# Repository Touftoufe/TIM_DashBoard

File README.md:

# TIM_DashBoard
TIM's new cars' dashboards

## Project Information

## Organization tree
 
 - hardware 
    - doc
        - BOM
        - appnotes
        - datasheets
        - errata
    - kicad
        - [inventhub git](https://inventhub.io/c/elprincipito/TIM_DashBoard/tree/default) (hardware versions management) 
        - project library
        - schematic
        - layout
    - meca
        - 3d models
        - gerber
- software
    - STM32CubeIDE project*  
- documentation
    - Block diagram
    - ICD (Interface control document)
    - User manual
    - Pinion diagram

## 'Requirements' specification

### Indispensable requirements
- See `actual` speed on screen
- Switch headlight on or off
- Signal turn (left, right, switch off)
- Wipe the windshield
- See break light status on screen
- Select wiper speed
- Select power level

### Optional requirements
- Select speed limit
- See set speed limit on screen
- Choose to drive forward or in reverse
- Turn car on/Off
- Configuration interface to choose between different modes

### Out of scope
- Klaxon

##  Progress status 
- [x] Organize the project
- [x] Have a clear idea of what to make
- [x] Test all hardware functions on prototype board
- [x] Correct the mistakes on prototype board 
- [x] Write and update Errata (/hardware/doc/errata.md)
- [x] Complete the specifications
- [ ] Translate the specifications into sequence diagram
- [ ] Start software for different functions
    - [ ] epaper screen control
    - [ ] servo motor control
    - [ ] speed limit input
    - [ ] menu navigation
    - [ ] *gpio* Lights control
    - [ ] *gpio* ...
- [ ] Document the [source code](/software) 
- [ ] Pass the tests
- [ ] write a User manual 
- [ ] Insatll new dashboard in the car 

## Contributors 
[Aouci Sofiane](https://www.linkedin.com/in/sofiane-aouci/) 

[Jacquet Prince](http://www.jacquet.live)

For Team : [TIM UPS INSA](http://www.timupsinsa.com)

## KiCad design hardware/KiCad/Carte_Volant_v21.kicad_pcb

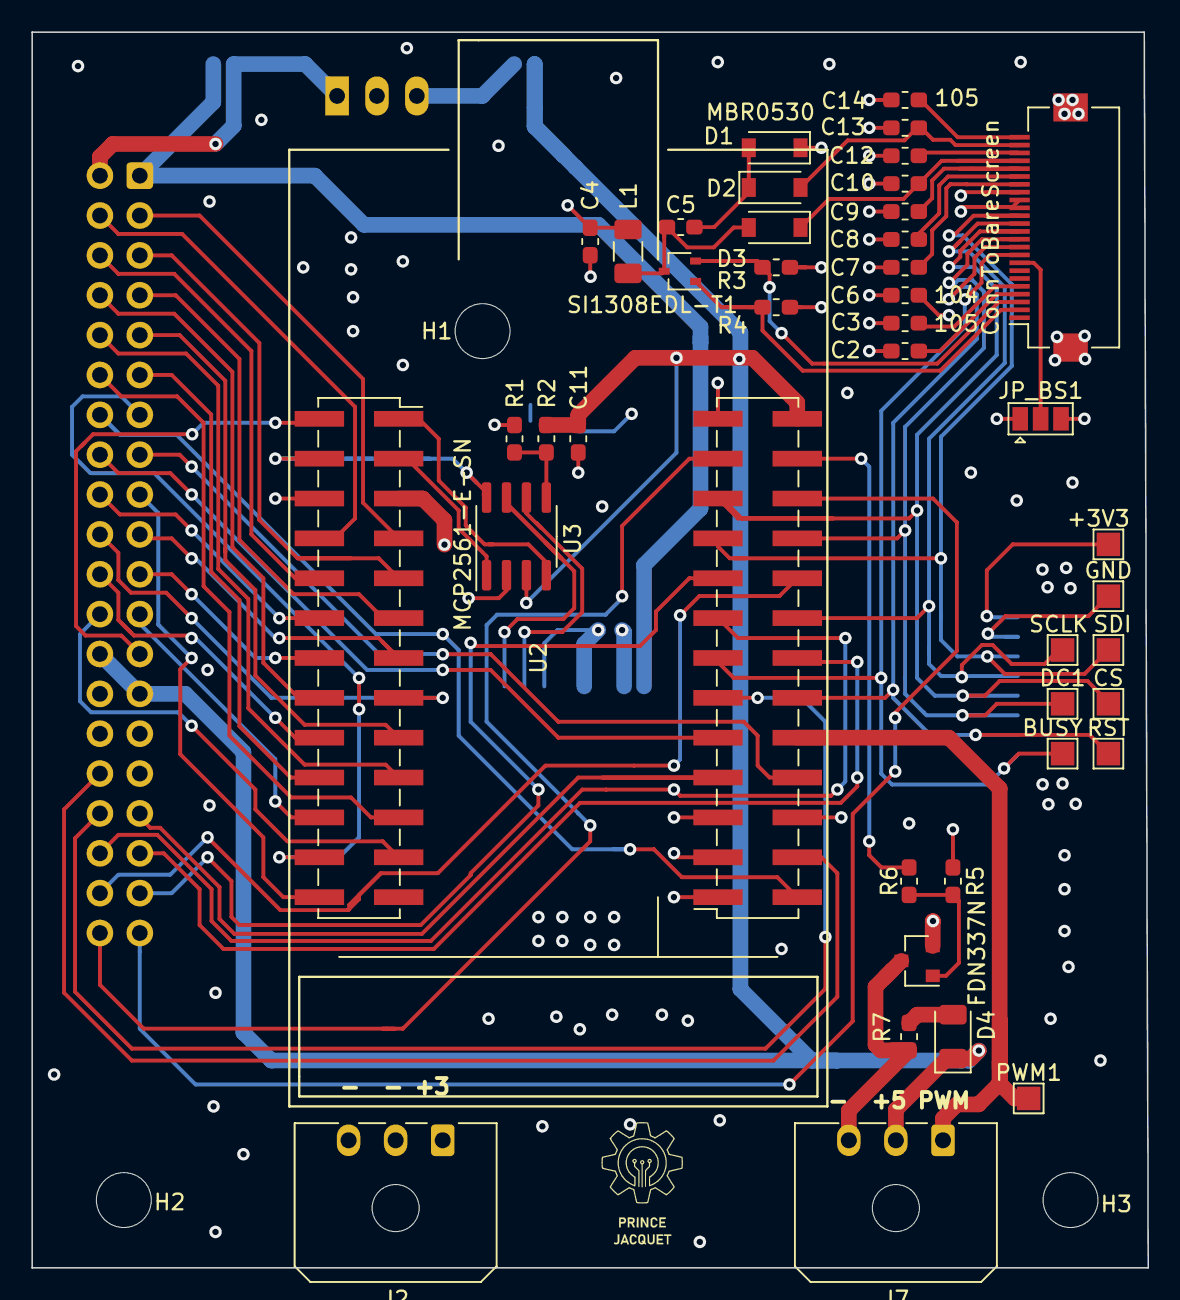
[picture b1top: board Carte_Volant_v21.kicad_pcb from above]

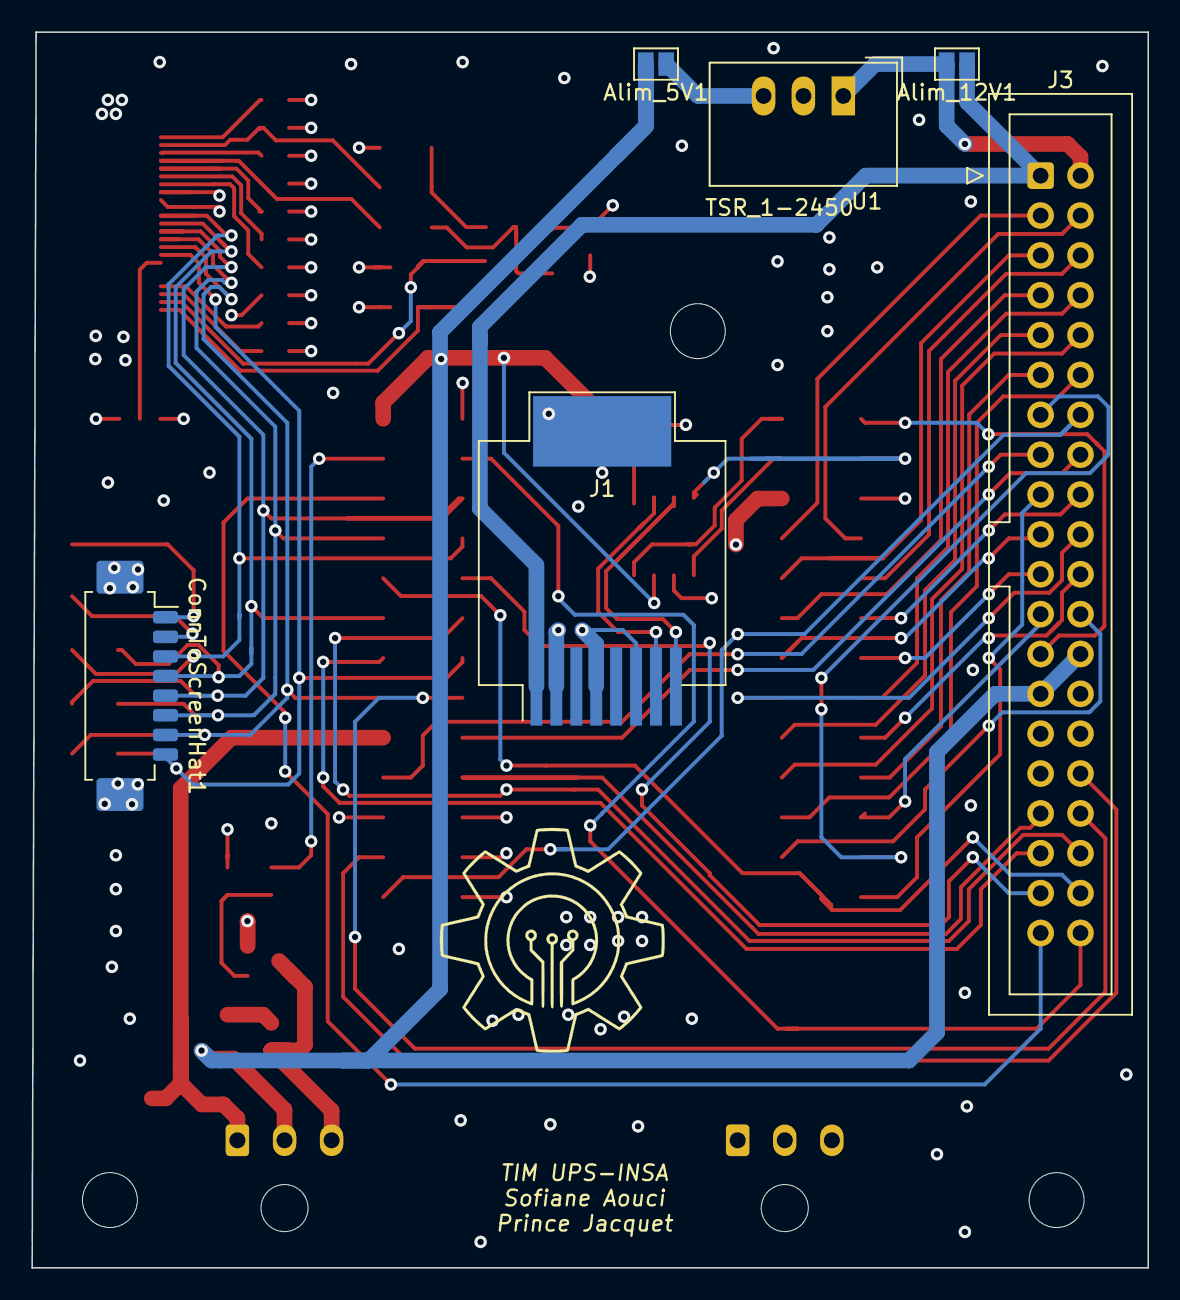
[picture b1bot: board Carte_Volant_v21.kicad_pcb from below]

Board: 4 copper layers, 71.1 x 78.7 mm, 51 parts (6 on the bottom side), 69 nets.

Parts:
+3V3: TestPoint; TestPoint_Pad_1.5x1.5mm
Alim_5V1, Alim_12V1: Jumper_NO_Small; SolderJumper-2_P1.3mm_Open_Pad1.0x1.5mm
BUSY: TestPoint; TestPoint_Pad_1.5x1.5mm
C2, C3, C7, C8, C9, C10, C12, C13, C14: 105; C_0603_1608Metric_Pad1.05x0.95mm_HandSolder
C4, C5: 4.7u; C_0603_1608Metric_Pad1.05x0.95mm_HandSolder
C6: 104; C_0603_1608Metric_Pad1.05x0.95mm_HandSolder
C11: 100n; C_0603_1608Metric_Pad1.05x0.95mm_HandSolder
CS: TestPoint; TestPoint_Pad_1.5x1.5mm
ConnToBareScreen: FFC_PFC_Conn_01x24_0.5MM; Hirose_FH12-24S-0.5SH_1x24-1MP_P0.50mm_Horizontal
ConnToScreenHat1: Conn_01x08; Molex_PicoBlade_53261-0871_1x08-1MP_P1.25mm_Horizontal
D1, D2, D3: MBR0530; D_SOD-123
D4: D; D_1206_3216Metric
DC1: TestPoint; TestPoint_Pad_1.5x1.5mm
GND: TestPoint; TestPoint_Pad_1.5x1.5mm
H1, H2, H3: MountingHole; MountingHole_3.5mm
J1: RJ45_CANBUS; RJ45_Molex_0855135013_Vertical
J2, J7: Conn_01x03; Molex_Micro-Fit_3.0_43650-0300_1x03_P3.00mm_Horizontal
J3: Conn_01x40; IDC-Header_2x20_P2.54mm_Vertical
JP_BS1: SolderJumper_3_Open; SolderJumper-3_P1.3mm_Open_Pad1.0x1.5mm
L1: L_Core_Ferrite; L_1206_3216Metric
PWM1: TestPoint; TestPoint_Pad_1.5x1.5mm
Q2: FDN337N; SOT-23
R1, R2, R4, R5, R7: 10k; R_0603_1608Metric_Pad1.05x0.95mm_HandSolder
R3: 47r; R_0603_1608Metric_Pad1.05x0.95mm_HandSolder
R6: 10; R_0603_1608Metric_Pad1.05x0.95mm_HandSolder
RST: TestPoint; TestPoint_Pad_1.5x1.5mm
SCLK: TestPoint; TestPoint_Pad_1.5x1.5mm
SDI: TestPoint; TestPoint_Pad_1.5x1.5mm
SI1308EDL-T1: Si1304BDL; SOT-323_SC-70
U1: TSR_1-2450; Converter_DCDC_TRACO_TSR-1_THT
U2: STM32H103-OlimexBoard; STM32H103-Olimex_SMD
U3: MCP2561-E-SN; SOIC-8_3.9x4.9mm_P1.27mm

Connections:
5VUSB: J3.40, U2.49
+3V3: +3V3.1, C4.2, C6.2, ConnToBareScreen.15, ConnToBareScreen.16, ConnToScreenHat1.1, J2.1, J3.30, J3.31, JP_BS1.1, L1.1, U2.5, U2.27, U2.31
+5V: Alim_5V1.2, C11.2, D4.1, J3.26, J3.27, J7.2, R2.1, U2.52, U3.3
+12V: Alim_12V1.1, J1.8, J3.1
ADC_current_Selector: J3.4, U2.8
BRAKE: J3.6, U2.10
BS: ConnToBareScreen.8, JP_BS1.2
BUSY: BUSY.1, ConnToBareScreen.9, ConnToScreenHat1.8, U2.39
CANH: J1.1, U3.7
CANL: J1.2, U3.6
CAN_Rx: U2.1, U3.4
CAN_STBY: U2.4, U3.8
CAN_Tx: U2.3, U3.1
CS: CS.1, ConnToBareScreen.12, ConnToScreenHat1.5, U2.47
D_C: ConnToBareScreen.11, ConnToScreenHat1.6, DC1.1, U2.46
ENC_SpeedSelector_CCW: J3.9, U2.17
ENC_SpeedSelector_CW: J3.8, U2.16
ENC_SpeedSelector_ok: J3.7, U2.11
GDR: ConnToBareScreen.2, R4.1, SI1308EDL-T1.1
GND: C2.1, C3.1, C4.1, C6.1, C7.1, C8.1, C9.1, C10.1, C11.1, C12.1, C13.1, C14.1, ConnToBareScreen.17, ConnToScreenHat1.2, D1.1, GND.1, J1.3, J1.5, J1.7, J1.L, J2.2, J2.3, J3.28, J3.29, JP_BS1.3, Q2.2, R1.2, R3.2, R4.2, R5.1, U1.2, U2.6, U2.29, U2.32, U2.51, U3.2
LIGHTS_Back: J3.11, U2.20
LIGHTS_Front: J3.10, U2.19
Marche_AVNT-ARRIER: J3.3, U2.7
unnamed: Alim_5V1.1, U1.3
unnamed: C5.1, D3.2, L1.2, SI1308EDL-T1.3
unnamed: C5.2, D1.2, D2.1
unnamed: D4.2, R7.1
unnamed: J7.3, Q2.3, R7.2
unnamed: Q2.1, R5.2, R6.1
unnamed: R1.1, R2.2, U3.5
PA0: J3.32, U2.30
PA2: J3.33, U2.33
PA4: J3.34, U2.37
PA5: J3.22, U2.18
PA6: J3.21, U2.14
PA7: J3.23, U2.22
PA8: J3.25, U2.2
PB5: J3.18, U2.12
PB6: J3.19, U2.13
PB7: J3.20, U2.15
PB10: J3.35, U2.40
PB11: J3.36, U2.41
PB12: J3.37, U2.43
PB14: J3.38, U2.44
PC8: J3.39, U2.48
POWER_SWITCH: Alim_12V1.2, J3.2, U1.1
PREVGH: C10.2, ConnToBareScreen.21, D3.1
PREVGL: C13.2, ConnToBareScreen.23, D2.2
PWM_wiper: J7.1, PWM1.1, U2.36
RESE: ConnToBareScreen.3, R3.1, SI1308EDL-T1.2
RST: ConnToBareScreen.10, ConnToScreenHat1.7, RST.1, U2.38
SCLK: ConnToBareScreen.13, ConnToScreenHat1.4, SCLK.1, U2.42
SDI: ConnToBareScreen.14, ConnToScreenHat1.3, SDI.1, U2.45
TURN_Sgnl_LEFT: J3.13, U2.24
TURN_Sgnl_RIGHT: J3.12, U2.21
VBAT: J3.24, U2.23
VCOM: C14.2, ConnToBareScreen.24
VDD: C7.2, ConnToBareScreen.18
VGH: C3.2, ConnToBareScreen.5
VGL: C2.2, ConnToBareScreen.4
VPP: C8.2, ConnToBareScreen.19
VSH: C9.2, ConnToBareScreen.20
VSL: C12.2, ConnToBareScreen.22
accelerateur: J3.5, U2.9
menu_down: J3.16, U2.35
menu_ok: J3.14, U2.28
menu_up: J3.15, U2.34
power_wiper: R6.2, U2.50
wiper_speed: J3.17, U2.26

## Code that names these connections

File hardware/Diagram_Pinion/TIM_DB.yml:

name: Carte_Volant_v21  # Put the name of diagram here
description: Example diagram # Put a short description of the diagram here
components:
    J1:
        description: RJ45_CANBUS_copy  # Arbitrary comment
        groups: [] # Specify component groups
        pins:
            L:  # Connected to GND
                name: J1.L
                description: ''
                groups: []
            '8': # Connected to -POWER_ON-OFF
                name: J1.8
                description: ''
                groups: []
            '7': # Connected to GND
                name: J1.7
                description: ''
                groups: []
            '6': # Connected to Net-(J1-Pad6)
                name: J1.6
                description: ''
                groups: []
            '5': # Connected to GND
                name: J1.5
                description: ''
                groups: []
            '4': # Connected to Net-(J1-Pad4)
                name: J1.4
                description: ''
                groups: []
            '3': # Connected to GND
                name: J1.3
                description: ''
                groups: []
            '2': # Connected to CANL
                name: J1.2
                description: ''
                groups: []
            '1': # Connected to CANH
                name: J1.1
                description: ''
                groups: []
        highlight: false # Make the component active
    U2:
        description: STM32H103-OlimexBoard  # Arbitrary comment
        groups: [] # Specify component groups
        pins:
            '27':  # Connected to +3V3
                name: U2.27
                description: ''
                groups: []
            '50': # Connected to power_wiper
                name: U2.50
                description: ''
                groups: []
            '48': # Connected to PC8
                name: U2.48
                description: ''
                groups: []
            '37': # Connected to PA4
                name: U2.37
                description: ''
                groups: []
            '34': # Connected to menu_up
                name: U2.34
                description: ''
                groups: []
            '47': # Connected to CS
                name: U2.47
                description: ''
                groups: []
            '45': # Connected to SDI
                name: U2.45
                description: ''
                groups: []
            '40': # Connected to PB10
                name: U2.40
                description: ''
                groups: []
            '36': # Connected to PWM_wiper
                name: U2.36
                description: ''
                groups: []
            '28': # Connected to menu_ok
                name: U2.28
                description: ''
                groups: []
            '29': # Connected to GND
                name: U2.29
                description: ''
                groups: []
            '49': # Connected to 5VUSB
                name: U2.49
                description: ''
                groups: []
            '33': # Connected to PA2
                name: U2.33
                description: ''
                groups: []
            '42': # Connected to SCLK
                name: U2.42
                description: ''
                groups: []
            '31': # Connected to +3V3
                name: U2.31
                description: ''
                groups: []
            '39': # Connected to BUSY
                name: U2.39
                description: ''
                groups: []
            '38': # Connected to RST
                name: U2.38
                description: ''
                groups: []
            '46': # Connected to D_C
                name: U2.46
                description: ''
                groups: []
            '41': # Connected to PB11
                name: U2.41
                description: ''
                groups: []
            '32': # Connected to GND
                name: U2.32
                description: ''
                groups: []
            '30': # Connected to PA0
                name: U2.30
                description: ''
                groups: []
            '44': # Connected to PB14
                name: U2.44
                description: ''
                groups: []
            '43': # Connected to PB12
                name: U2.43
                description: ''
                groups: []
            '35': # Connected to menu_down
                name: U2.35
                description: ''
                groups: []
            '52': # Connected to +5V
                name: U2.52
                description: ''
                groups: []
            '51': # Connected to GND
                name: U2.51
                description: ''
                groups: []
            '1': # Connected to CAN_Rx
                name: U2.1
                description: ''
                groups: []
            '24': # Connected to TURN_Sgnl_LEFT
                name: U2.24
                description: ''
                groups: []
            '22': # Connected to PA7
                name: U2.22
                description: ''
                groups: []
            '11': # Connected to ENC_SpeedSelector_ok
                name: U2.11
                description: ''
                groups: []
            '8': # Connected to ADC_current_Selector
                name: U2.8
                description: ''
                groups: []
            '21': # Connected to TURN_Sgnl_RIGHT
                name: U2.21
                description: ''
                groups: []
            '19': # Connected to LIGHTS_Front
                name: U2.19
                description: ''
                groups: []
            '14': # Connected to PA6
                name: U2.14
                description: ''
                groups: []
            '10': # Connected to BRAKE
                name: U2.10
                description: ''
                groups: []
            '2': # Connected to PA8
                name: U2.2
                description: ''
                groups: []
            '3': # Connected to CAN_Tx
                name: U2.3
                description: ''
                groups: []
            '23': # Connected to VBAT
                name: U2.23
                description: ''
                groups: []
            '7': # Connected to Marche_AVNT-ARRIER
                name: U2.7
                description: ''
                groups: []
            '16': # Connected to ENC_SpeedSelector_CW
                name: U2.16
                description: ''
                groups: []
            '5': # Connected to +3V3
                name: U2.5
                description: ''
                groups: []
            '13': # Connected to PB6
                name: U2.13
                description: ''
                groups: []
            '12': # Connected to PB5
                name: U2.12
                description: ''
                groups: []
            '20': # Connected to LIGHTS_Back
                name: U2.20
                description: ''
                groups: []
            '15': # Connected to PB7
                name: U2.15
                description: ''
                groups: []
            '6': # Connected to GND
                name: U2.6
                description: ''
                groups: []
            '4': # Connected to CAN_STBY
                name: U2.4
                description: ''
                groups: []
            '18': # Connected to PA5
                name: U2.18
                description: ''
                groups: []
            '17': # Connected to ENC_SpeedSelector_CCW
                name: U2.17
                description: ''
                groups: []
            '9': # Connected to accelerateur
                name: U2.9
                description: ''
                groups: []
            '26': # Connected to wiper_speed
                name: U2.26
                description: ''
                groups: []
            '25': # Connected to ST_RST
                name: U2.25
                description: ''
                groups: []
        highlight: false # Make the component active

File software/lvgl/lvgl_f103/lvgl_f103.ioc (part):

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Mcu.Name=STM32F103R(8-B)Tx
Mcu.Package=LQFP64
Mcu.UserName=STM32F103RBTx
PA11.Mode=CAN_Activate
PA11.Signal=CAN_RX
PA12.Mode=CAN_Activate
PA12.Signal=CAN_TX
PA13.Mode=Serial_Wire
PA13.Signal=SYS_JTMS-SWDIO
PA14.Mode=Serial_Wire
PA14.Signal=SYS_JTCK-SWCLK
PA3.GPIOParameters=GPIO_Label
PA3.GPIO_Label=timer_pwm
PA3.Signal=S_TIM2_CH4
PA4.GPIOParameters=GPIO_Label
PA4.GPIO_Label=CurrentSelector
PA4.Signal=SharedAnalog_PA4
PA5.Mode=Full_Duplex_Master
PA5.Signal=SPI1_SCK
PA6.Mode=Full_Duplex_Master
PA6.Signal=SPI1_MISO
PA7.Mode=Full_Duplex_Master
PA7.Signal=SPI1_MOSI
PA9.GPIOParameters=GPIO_Label
PA9.GPIO_Label=CAN_STBY
PA9.Signal=GPIO_Output
PB0.GPIOParameters=GPIO_Label
PB0.GPIO_Label=LCD_RST
PB0.Signal=GPIO_Output
PB10.GPIOParameters=GPIO_Label
PB10.GPIO_Label=LCD_DC
PB10.Signal=GPIO_Output
PB12.GPIOParameters=GPIO_PuPd,GPIO_Label,GPIO_ModeDefaultEXTI
PB12.GPIO_Label=WiperStateB
PB12.GPIO_ModeDefaultEXTI=GPIO_MODE_IT_RISING_FALLING
PB12.GPIO_PuPd=GPIO_PULLUP
PB12.Signal=GPXTI12
PB14.GPIOParameters=GPIO_PuPd,GPIO_Label,GPIO_ModeDefaultEXTI
PB14.GPIO_Label=WiperStateA
PB14.GPIO_ModeDefaultEXTI=GPIO_MODE_IT_RISING_FALLING
PB14.GPIO_PuPd=GPIO_PULLUP
PB14.Signal=GPXTI14
PB5.GPIOParameters=GPIO_PuPd,GPIO_Label,GPIO_ModeDefaultEXTI
PB5.GPIO_Label=Left_TurnSignal
PB5.GPIO_ModeDefaultEXTI=GPIO_MODE_IT_RISING_FALLING
PB5.GPIO_PuPd=GPIO_PULLUP
PB5.Signal=GPXTI5
PB6.GPIOParameters=GPIO_PuPd,GPIO_Label,GPIO_ModeDefaultEXTI
PB6.GPIO_Label=Right_TurnSignal
PB6.GPIO_ModeDefaultEXTI=GPIO_MODE_IT_RISING_FALLING
PB6.GPIO_PuPd=GPIO_PULLUP
PB6.Signal=GPXTI6
PC1.GPIOParameters=GPIO_PuPd,GPIO_Label,GPIO_ModeDefaultEXTI
PC1.GPIO_Label=HeadLight
PC1.GPIO_ModeDefaultEXTI=GPIO_MODE_IT_RISING_FALLING
PC1.GPIO_PuPd=GPIO_PULLUP
PC1.Signal=GPXTI1
PC12.GPIOParameters=GPIO_Label
PC12.GPIO_Label=LED
PC12.Signal=GPIO_Output
PC5.GPIOParameters=GPIO_Label
PC5.GPIO_Label=SPI_CS
PC5.Signal=GPIO_Output
PC8.GPIOParameters=GPIO_PuPd,GPIO_Label,GPIO_ModeDefaultEXTI
PC8.GPIO_Label=BreakPedal
PC8.GPIO_ModeDefaultEXTI=GPIO_MODE_IT_RISING_FALLING
PC8.GPIO_PuPd=GPIO_PULLUP
PC8.Signal=GPXTI8
PD0-OSC_IN.Mode=HSE-External-Oscillator
PD0-OSC_IN.Signal=RCC_OSC_IN
PD1-OSC_OUT.Mode=HSE-External-Oscillator
PD1-OSC_OUT.Signal=RCC_OSC_OUT
PD2.GPIOParameters=GPIO_PuPd,GPIO_Label,GPIO_ModeDefaultEXTI
PD2.GPIO_Label=Accelerator
PD2.GPIO_ModeDefaultEXTI=GPIO_MODE_IT_RISING_FALLING
PD2.GPIO_PuPd=GPIO_PULLUP
PD2.Signal=GPXTI2
RCC.SYSCLKFreq_VALUE=72000000
RCC.SYSCLKSource=RCC_SYSCLKSOURCE_PLLCLK
board=custom

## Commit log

2021-05-09 Create LICENSE
2021-05-09 added hardware
2021-05-15 add 'test' to README.md
2021-05-15 draft of directory structure in README.md
2021-05-15 format
2021-05-15 added gerber folder
2021-06-12 errata correction : RJ45 connector + common volatge source + added 3d models + logo + ...
2021-06-12 Corrected from Errata : RJ45 connector + common voltage silks screen + schematics organisation + added 3D models + Logo
2021-06-29 added documentation folder
2021-06-29 repository ready for work
2021-06-29 correct Readme contributors
2021-09-03 doc:readme.md - added new readme.md for devs - describe hardware setup and boards - explain can tools and configurations
2021-09-21 can mmessages and wiper working
2021-09-22 requirements: starting to design the software architecture - List most of the requirements - Started a .md Sequence Diagram file
2021-09-22 replace sequence_diagrams.md
2021-09-24 Global specifications complete
2021-11-05 add user can module and wiper module
2022-01-25 working CAN send and receive + DMA everywhere + ADC reading for speed selection + ... (wiper do not work anymore)
2022-01-27 LVGL porting
    - Porting LVGL library to an stm32f429.
    - Writing ILI1931 LCD display driver (spi interface with DMA)
    On branch LVGL_test
    Initial commit
    Changes to be committed:
    new file: .cproject
2022-01-29 test and verify wiper code : sucessful command with wiper problem was in the harware
2022-02-05 move every functions of model to model.c/.h
2022-02-25 New software locally merge screen control and model code
2022-03-19 added new inputs
2022-03-20 Created the view deleted: software/lvgl/lvgl_f103/Core/Inc/Testboard_ui.h modified: software/lvgl/lvgl_f103/Core/Inc/view.h deleted: software/lvgl/lvgl_f103/Core/Src/Testboard_ui.c deleted: software/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
2022-03-20 added .gitignore
2022-03-20 Removed Release dir
2022-03-29 code to be tested on hardware
2022-04-16 validta ADC and speed
2022-05-07 switch pc
2022-05-07 beta fully functionnal mvp
2022-05-14 clean code base (in going)
2022-11-18 miising final test and updates (break,wiper,robust blink)
